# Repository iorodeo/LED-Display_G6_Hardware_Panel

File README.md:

## LED-Display\_ G6\_Hardware\_Panel 

This repository is part of <https://reiserlab.github.io/Modular-LED-Display/>.
It contains the KiCad design and production files for the G6 panel hardware.

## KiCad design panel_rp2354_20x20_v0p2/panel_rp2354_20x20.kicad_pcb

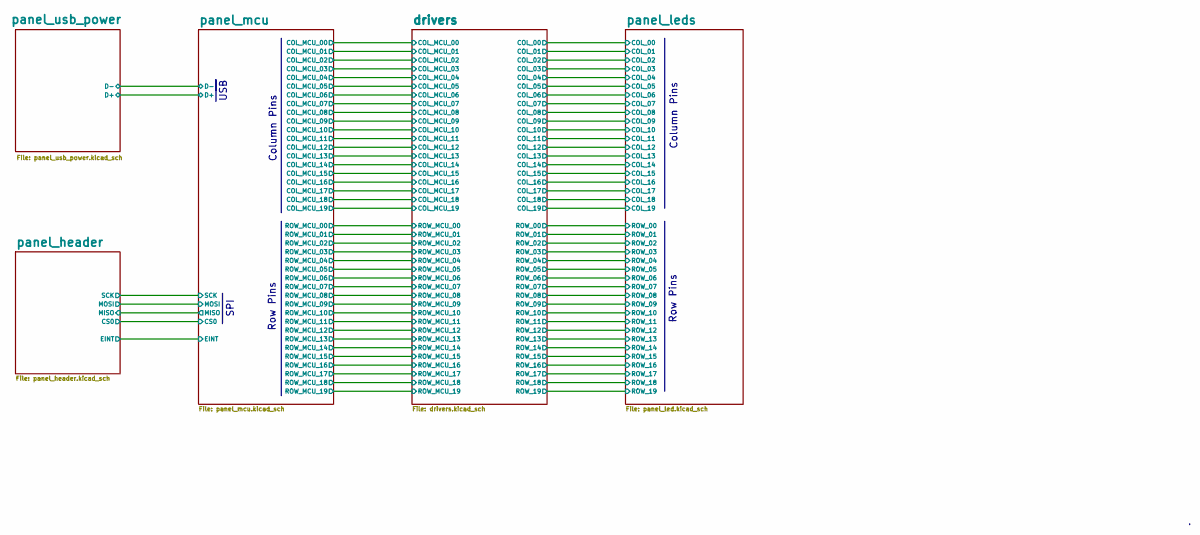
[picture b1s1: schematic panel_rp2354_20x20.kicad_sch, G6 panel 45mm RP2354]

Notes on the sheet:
Column Pins
Row Pins
SPI
USB

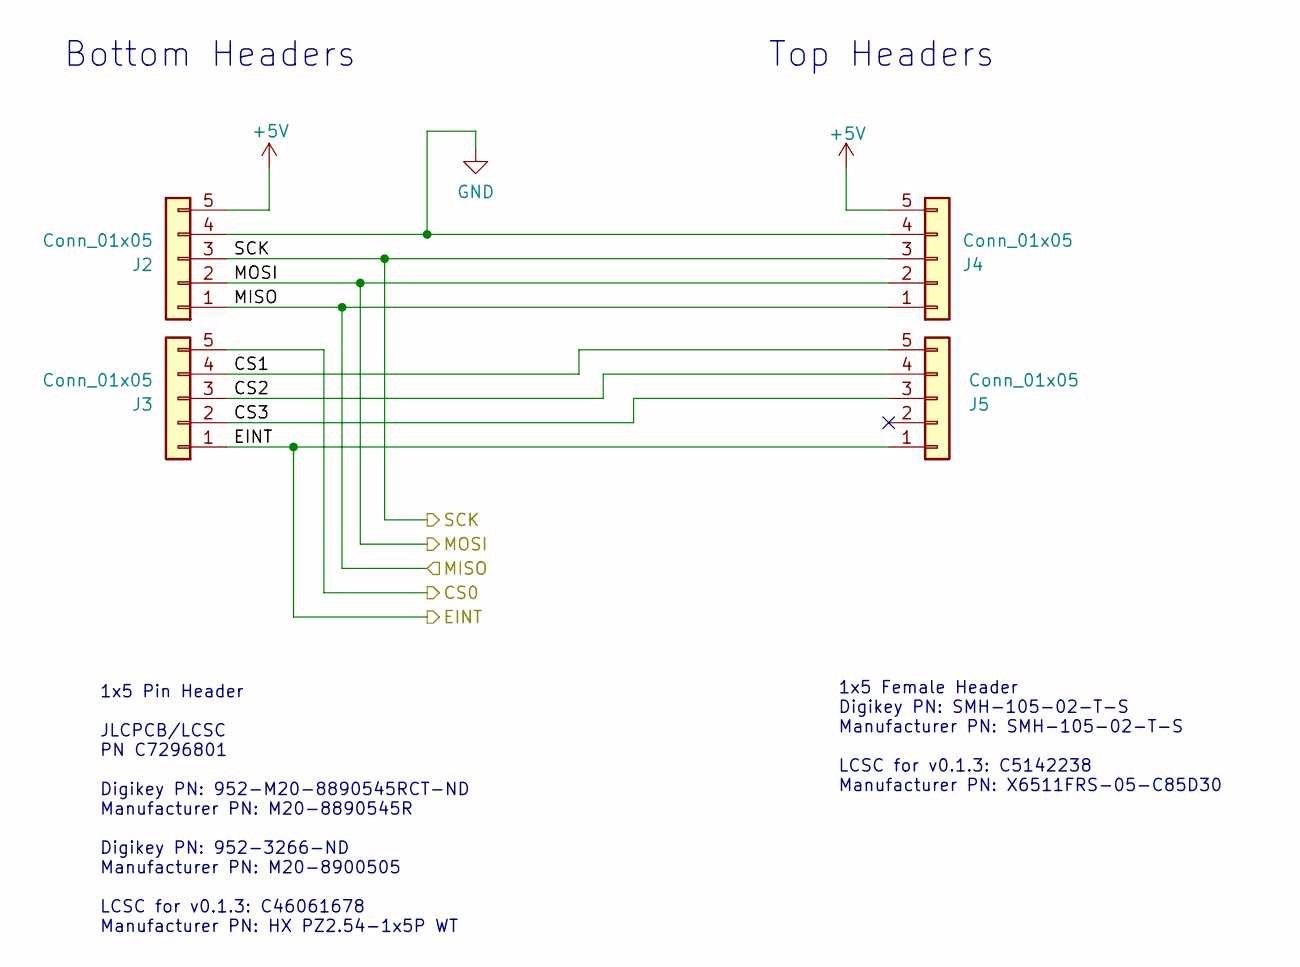
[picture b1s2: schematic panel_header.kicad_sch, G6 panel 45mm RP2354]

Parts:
J2, J3: Conn_01x05; PinHeader_1x5_M20-8890545R; LCSC Part # C46061678
J4, J5: Conn_01x05; ConnRcpt_1x5_SMH-105-02-X-S; LCSC Part # C5142238

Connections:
+5V: J2.5, J4.5; also elsewhere on the board
/panel_header/CS0: J3.5; also elsewhere on the board
/panel_header/CS1: J3.4, J5.5
/panel_header/CS2: J3.3, J5.4
/panel_header/CS3: J3.2, J5.3
/panel_header/EINT: J3.1, J5.1; also elsewhere on the board
/panel_header/MISO: J2.1, J4.1; also elsewhere on the board
/panel_header/MOSI: J2.2, J4.2; also elsewhere on the board
/panel_header/SCK: J2.3, J4.3; also elsewhere on the board
GND: J2.4, J4.4; also elsewhere on the board

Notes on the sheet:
1x5 Pin Header JLCPCB/LCSC PN C7296801 Digikey PN: 952-M20-8890545RCT-ND Manufacturer PN: M20-8890545R Digikey PN: 952-3266-ND Manufacturer PN: M20-8900505 LCSC for v0.1.3: C46061678 Manufacturer PN: HX PZ2.54-1x5P WT
Top Headers
1x5 Female Header Digikey PN: SMH-105-02-T-S Manufacturer PN: SMH-105-02-T-S LCSC for v0.1.3: C5142238 Manufacturer PN: X6511FRS-05-C85D30
Bottom Headers

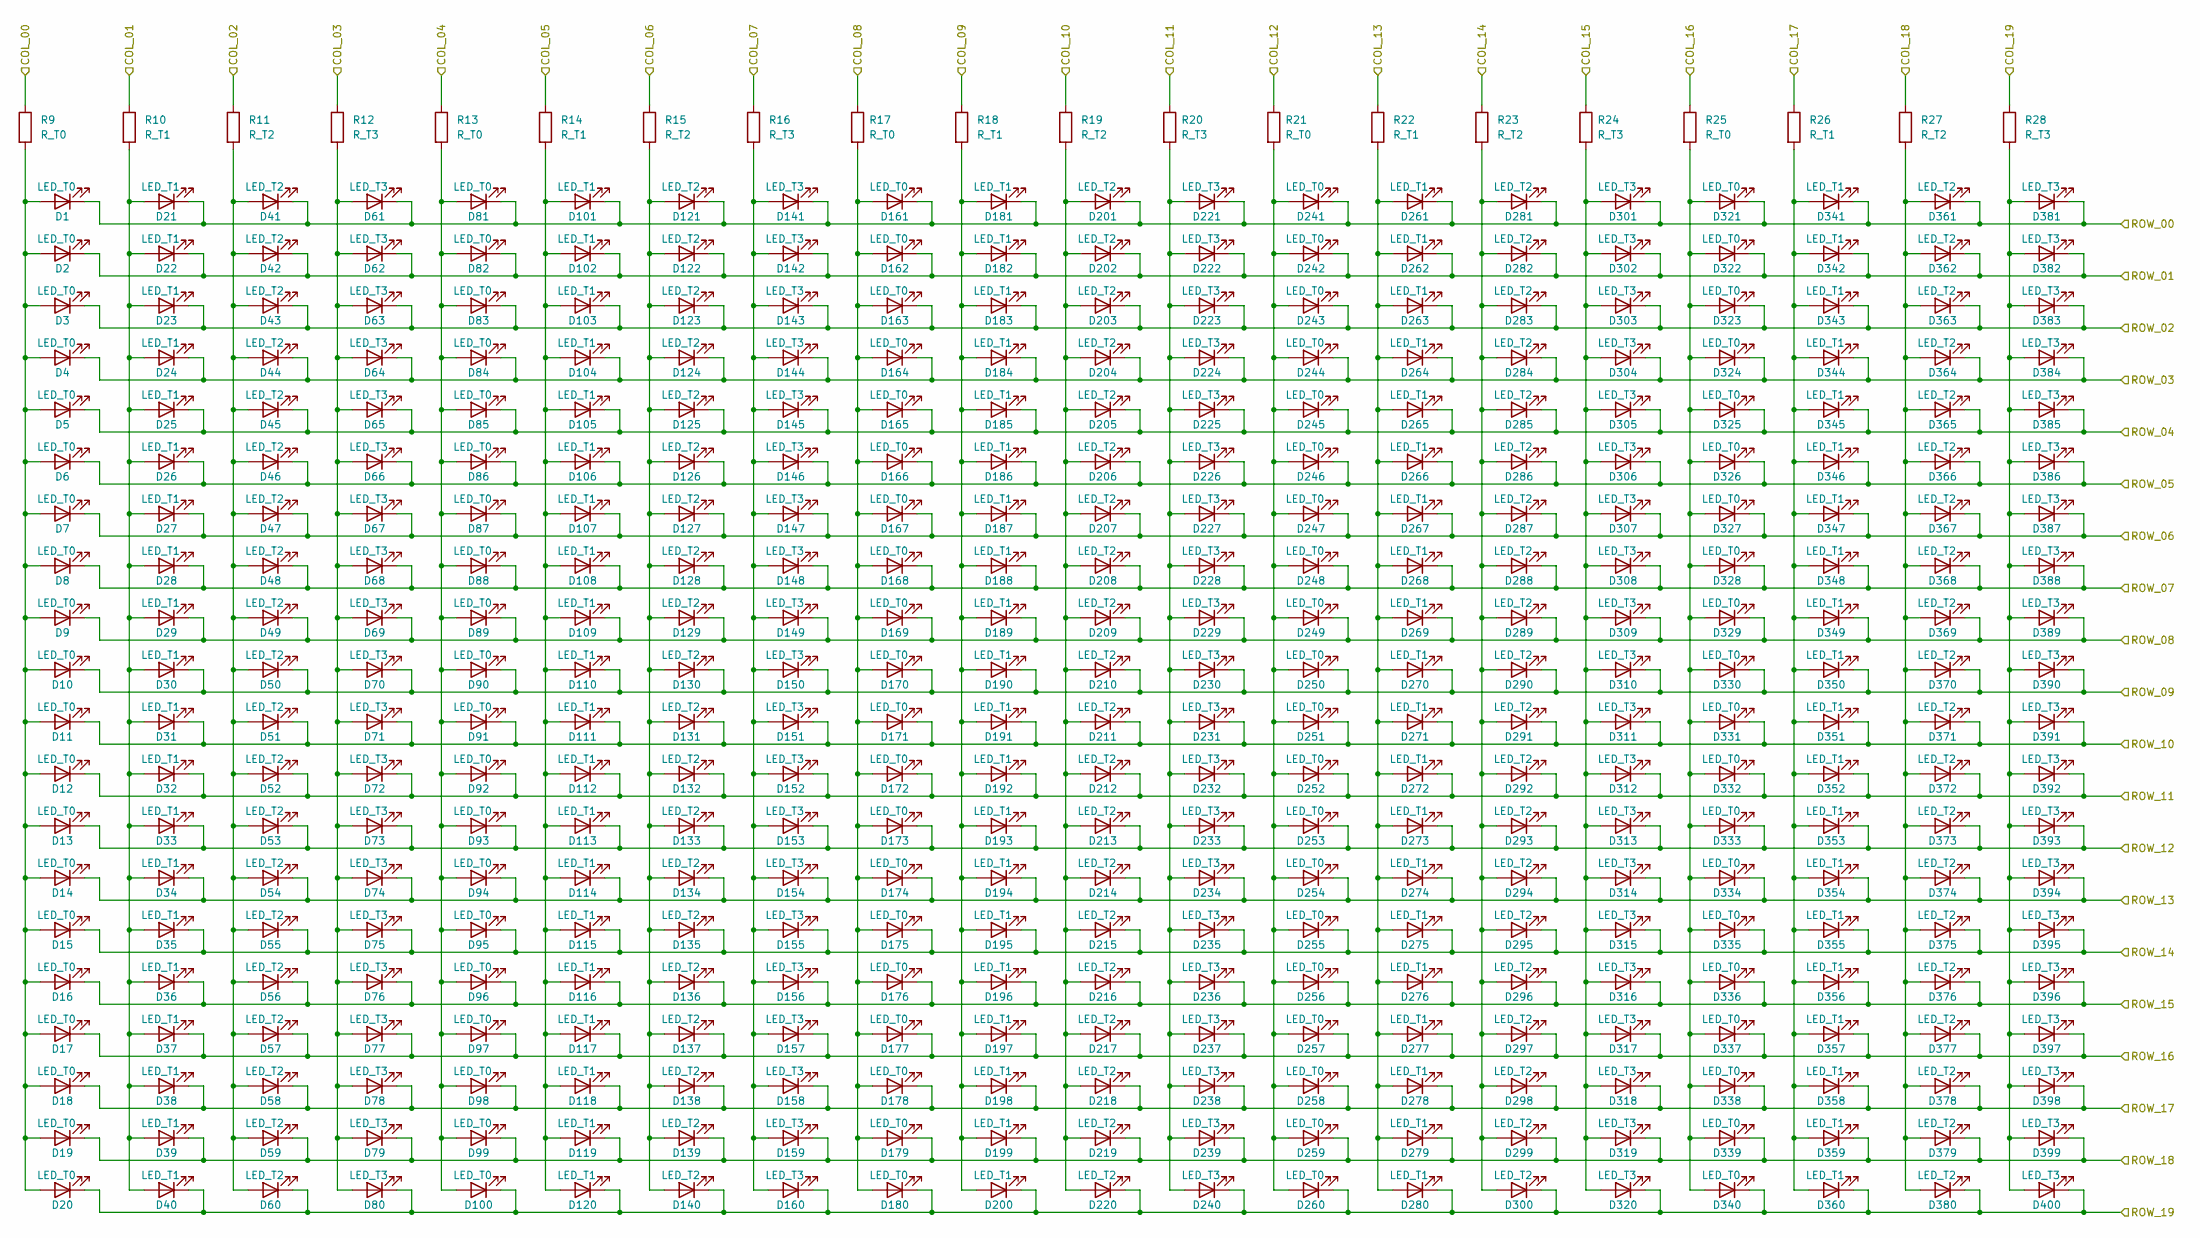
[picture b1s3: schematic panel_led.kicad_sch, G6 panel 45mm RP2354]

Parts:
D1, D2, D3, D4, D5, D6, D7, D8, D9, D10, D11, D12, D13, D14, D15, D16, D17, D18, D19, D20, D81, D82, D83, D84, D85, D86, D87, D88, D89, D90, D91, D92, D93, D94, D95, D96, D97, D98, D99, D100, D161, D162, D163, D164, D165, D166, D167, D168, D169, D170, D171, D172, D173, D174, D175, D176, D177, D178, D179, D180, D241, D242, D243, D244, D245, D246, D247, D248, D249, D250, D251, D252, D253, D254, D255, D256, D257, D258, D259, D260, D321, D322, D323, D324, D325, D326, D327, D328, D329, D330, D331, D332, D333, D334, D335, D336, D337, D338, D339, D340: LED_T0; LED_0402_1005Metric; LCSC Part # C9900113976
D21, D22, D23, D24, D25, D26, D27, D28, D29, D30, D31, D32, D33, D34, D35, D36, D37, D38, D39, D40, D101, D102, D103, D104, D105, D106, D107, D108, D109, D110, D111, D112, D113, D114, D115, D116, D117, D118, D119, D120, D181, D182, D183, D184, D185, D186, D187, D188, D189, D190, D191, D192, D193, D194, D195, D196, D197, D198, D199, D200, D261, D262, D263, D264, D265, D266, D267, D268, D269, D270, D271, D272, D273, D274, D275, D276, D277, D278, D279, D280, D341, D342, D343, D344, D345, D346, D347, D348, D349, D350, D351, D352, D353, D354, D355, D356, D357, D358, D359, D360: LED_T1; LED_0402_1005Metric; LCSC Part # C9900113976
D41, D42, D43, D44, D45, D46, D47, D48, D49, D50, D51, D52, D53, D54, D55, D56, D57, D58, D59, D60, D121, D122, D123, D124, D125, D126, D127, D128, D129, D130, D131, D132, D133, D134, D135, D136, D137, D138, D139, D140, D201, D202, D203, D204, D205, D206, D207, D208, D209, D210, D211, D212, D213, D214, D215, D216, D217, D218, D219, D220, D281, D282, D283, D284, D285, D286, D287, D288, D289, D290, D291, D292, D293, D294, D295, D296, D297, D298, D299, D300, D361, D362, D363, D364, D365, D366, D367, D368, D369, D370, D371, D372, D373, D374, D375, D376, D377, D378, D379, D380: LED_T2; LED_0402_1005Metric; LCSC Part # C9900113976
D61, D62, D63, D64, D65, D66, D67, D68, D69, D70, D71, D72, D73, D74, D75, D76, D77, D78, D79, D80, D141, D142, D143, D144, D145, D146, D147, D148, D149, D150, D151, D152, D153, D154, D155, D156, D157, D158, D159, D160, D221, D222, D223, D224, D225, D226, D227, D228, D229, D230, D231, D232, D233, D234, D235, D236, D237, D238, D239, D240, D301, D302, D303, D304, D305, D306, D307, D308, D309, D310, D311, D312, D313, D314, D315, D316, D317, D318, D319, D320, D381, D382, D383, D384, D385, D386, D387, D388, D389, D390, D391, D392, D393, D394, D395, D396, D397, D398, D399, D400: LED_T3; LED_0402_1005Metric; LCSC Part # C9900113976
R9, R13, R17, R21, R25: R_T0; R_0201_0603Metric; LCSC Part # C851657
R10, R14, R18, R22, R26: R_T1; R_0201_0603Metric; LCSC Part # C851657
R11, R15, R19, R23, R27: R_T2; R_0201_0603Metric; LCSC Part # C851657
R12, R16, R20, R24, R28: R_T3; R_0201_0603Metric; LCSC Part # C851657

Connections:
/drivers/COL_00: R9.1; also elsewhere on the board
/drivers/COL_01: R10.1; also elsewhere on the board
/drivers/COL_02: R11.1; also elsewhere on the board
/drivers/COL_03: R12.1; also elsewhere on the board
/drivers/COL_04: R13.1; also elsewhere on the board
/drivers/COL_05: R14.1; also elsewhere on the board
/drivers/COL_06: R15.1; also elsewhere on the board
/drivers/COL_07: R16.1; also elsewhere on the board
/drivers/COL_08: R17.1; also elsewhere on the board
/drivers/COL_09: R18.1; also elsewhere on the board
/drivers/COL_10: R19.1; also elsewhere on the board
/drivers/COL_11: R20.1; also elsewhere on the board
/drivers/COL_12: R21.1; also elsewhere on the board
/drivers/COL_13: R22.1; also elsewhere on the board
/drivers/COL_14: R23.1; also elsewhere on the board
/drivers/COL_15: R24.1; also elsewhere on the board
/drivers/COL_16: R25.1; also elsewhere on the board
/drivers/COL_17: R26.1; also elsewhere on the board
/drivers/COL_18: R27.1; also elsewhere on the board
/drivers/COL_19: R28.1; also elsewhere on the board
/drivers/ROW_00: D1.1 (K), D21.1 (K), D41.1 (K), D61.1 (K), D81.1 (K), D101.1 (K), D121.1 (K), D141.1 (K), D161.1 (K), D181.1 (K), D201.1 (K), D221.1 (K), D241.1 (K), D261.1 (K), D281.1 (K), D301.1 (K), D321.1 (K), D341.1 (K), D361.1 (K), D381.1 (K); also elsewhere on the board
/drivers/ROW_01: D2.1 (K), D22.1 (K), D42.1 (K), D62.1 (K), D82.1 (K), D102.1 (K), D122.1 (K), D142.1 (K), D162.1 (K), D182.1 (K), D202.1 (K), D222.1 (K), D242.1 (K), D262.1 (K), D282.1 (K), D302.1 (K), D322.1 (K), D342.1 (K), D362.1 (K), D382.1 (K); also elsewhere on the board
/drivers/ROW_02: D3.1 (K), D23.1 (K), D43.1 (K), D63.1 (K), D83.1 (K), D103.1 (K), D123.1 (K), D143.1 (K), D163.1 (K), D183.1 (K), D203.1 (K), D223.1 (K), D243.1 (K), D263.1 (K), D283.1 (K), D303.1 (K), D323.1 (K), D343.1 (K), D363.1 (K), D383.1 (K); also elsewhere on the board
/drivers/ROW_03: D4.1 (K), D24.1 (K), D44.1 (K), D64.1 (K), D84.1 (K), D104.1 (K), D124.1 (K), D144.1 (K), D164.1 (K), D184.1 (K), D204.1 (K), D224.1 (K), D244.1 (K), D264.1 (K), D284.1 (K), D304.1 (K), D324.1 (K), D344.1 (K), D364.1 (K), D384.1 (K); also elsewhere on the board
/drivers/ROW_04: D5.1 (K), D25.1 (K), D45.1 (K), D65.1 (K), D85.1 (K), D105.1 (K), D125.1 (K), D145.1 (K), D165.1 (K), D185.1 (K), D205.1 (K), D225.1 (K), D245.1 (K), D265.1 (K), D285.1 (K), D305.1 (K), D325.1 (K), D345.1 (K), D365.1 (K), D385.1 (K); also elsewhere on the board
/drivers/ROW_05: D6.1 (K), D26.1 (K), D46.1 (K), D66.1 (K), D86.1 (K), D106.1 (K), D126.1 (K), D146.1 (K), D166.1 (K), D186.1 (K), D206.1 (K), D226.1 (K), D246.1 (K), D266.1 (K), D286.1 (K), D306.1 (K), D326.1 (K), D346.1 (K), D366.1 (K), D386.1 (K); also elsewhere on the board
/drivers/ROW_06: D7.1 (K), D27.1 (K), D47.1 (K), D67.1 (K), D87.1 (K), D107.1 (K), D127.1 (K), D147.1 (K), D167.1 (K), D187.1 (K), D207.1 (K), D227.1 (K), D247.1 (K), D267.1 (K), D287.1 (K), D307.1 (K), D327.1 (K), D347.1 (K), D367.1 (K), D387.1 (K); also elsewhere on the board
/drivers/ROW_07: D8.1 (K), D28.1 (K), D48.1 (K), D68.1 (K), D88.1 (K), D108.1 (K), D128.1 (K), D148.1 (K), D168.1 (K), D188.1 (K), D208.1 (K), D228.1 (K), D248.1 (K), D268.1 (K), D288.1 (K), D308.1 (K), D328.1 (K), D348.1 (K), D368.1 (K), D388.1 (K); also elsewhere on the board
/drivers/ROW_08: D9.1 (K), D29.1 (K), D49.1 (K), D69.1 (K), D89.1 (K), D109.1 (K), D129.1 (K), D149.1 (K), D169.1 (K), D189.1 (K), D209.1 (K), D229.1 (K), D249.1 (K), D269.1 (K), D289.1 (K), D309.1 (K), D329.1 (K), D349.1 (K), D369.1 (K), D389.1 (K); also elsewhere on the board
/drivers/ROW_09: D10.1 (K), D30.1 (K), D50.1 (K), D70.1 (K), D90.1 (K), D110.1 (K), D130.1 (K), D150.1 (K), D170.1 (K), D190.1 (K), D210.1 (K), D230.1 (K), D250.1 (K), D270.1 (K), D290.1 (K), D310.1 (K), D330.1 (K), D350.1 (K), D370.1 (K), D390.1 (K); also elsewhere on the board
/drivers/ROW_10: D11.1 (K), D31.1 (K), D51.1 (K), D71.1 (K), D91.1 (K), D111.1 (K), D131.1 (K), D151.1 (K), D171.1 (K), D191.1 (K), D211.1 (K), D231.1 (K), D251.1 (K), D271.1 (K), D291.1 (K), D311.1 (K), D331.1 (K), D351.1 (K), D371.1 (K), D391.1 (K); also elsewhere on the board
/drivers/ROW_11: D12.1 (K), D32.1 (K), D52.1 (K), D72.1 (K), D92.1 (K), D112.1 (K), D132.1 (K), D152.1 (K), D172.1 (K), D192.1 (K), D212.1 (K), D232.1 (K), D252.1 (K), D272.1 (K), D292.1 (K), D312.1 (K), D332.1 (K), D352.1 (K), D372.1 (K), D392.1 (K); also elsewhere on the board
/drivers/ROW_12: D13.1 (K), D33.1 (K), D53.1 (K), D73.1 (K), D93.1 (K), D113.1 (K), D133.1 (K), D153.1 (K), D173.1 (K), D193.1 (K), D213.1 (K), D233.1 (K), D253.1 (K), D273.1 (K), D293.1 (K), D313.1 (K), D333.1 (K), D353.1 (K), D373.1 (K), D393.1 (K); also elsewhere on the board
/drivers/ROW_13: D14.1 (K), D34.1 (K), D54.1 (K), D74.1 (K), D94.1 (K), D114.1 (K), D134.1 (K), D154.1 (K), D174.1 (K), D194.1 (K), D214.1 (K), D234.1 (K), D254.1 (K), D274.1 (K), D294.1 (K), D314.1 (K), D334.1 (K), D354.1 (K), D374.1 (K), D394.1 (K); also elsewhere on the board
/drivers/ROW_14: D15.1 (K), D35.1 (K), D55.1 (K), D75.1 (K), D95.1 (K), D115.1 (K), D135.1 (K), D155.1 (K), D175.1 (K), D195.1 (K), D215.1 (K), D235.1 (K), D255.1 (K), D275.1 (K), D295.1 (K), D315.1 (K), D335.1 (K), D355.1 (K), D375.1 (K), D395.1 (K); also elsewhere on the board
/drivers/ROW_15: D16.1 (K), D36.1 (K), D56.1 (K), D76.1 (K), D96.1 (K), D116.1 (K), D136.1 (K), D156.1 (K), D176.1 (K), D196.1 (K), D216.1 (K), D236.1 (K), D256.1 (K), D276.1 (K), D296.1 (K), D316.1 (K), D336.1 (K), D356.1 (K), D376.1 (K), D396.1 (K); also elsewhere on the board
/drivers/ROW_16: D17.1 (K), D37.1 (K), D57.1 (K), D77.1 (K), D97.1 (K), D117.1 (K), D137.1 (K), D157.1 (K), D177.1 (K), D197.1 (K), D217.1 (K), D237.1 (K), D257.1 (K), D277.1 (K), D297.1 (K), D317.1 (K), D337.1 (K), D357.1 (K), D377.1 (K), D397.1 (K); also elsewhere on the board
/drivers/ROW_17: D18.1 (K), D38.1 (K), D58.1 (K), D78.1 (K), D98.1 (K), D118.1 (K), D138.1 (K), D158.1 (K), D178.1 (K), D198.1 (K), D218.1 (K), D238.1 (K), D258.1 (K), D278.1 (K), D298.1 (K), D318.1 (K), D338.1 (K), D358.1 (K), D378.1 (K), D398.1 (K); also elsewhere on the board
/drivers/ROW_18: D19.1 (K), D39.1 (K), D59.1 (K), D79.1 (K), D99.1 (K), D119.1 (K), D139.1 (K), D159.1 (K), D179.1 (K), D199.1 (K), D219.1 (K), D239.1 (K), D259.1 (K), D279.1 (K), D299.1 (K), D319.1 (K), D339.1 (K), D359.1 (K), D379.1 (K), D399.1 (K); also elsewhere on the board
/drivers/ROW_19: D20.1 (K), D40.1 (K), D60.1 (K), D80.1 (K), D100.1 (K), D120.1 (K), D140.1 (K), D160.1 (K), D180.1 (K), D200.1 (K), D220.1 (K), D240.1 (K), D260.1 (K), D280.1 (K), D300.1 (K), D320.1 (K), D340.1 (K), D360.1 (K), D380.1 (K), D400.1 (K); also elsewhere on the board
unnamed: D1.2 (A), D2.2 (A), D3.2 (A), D4.2 (A), D5.2 (A), D6.2 (A), D7.2 (A), D8.2 (A), D9.2 (A), D10.2 (A), D11.2 (A), D12.2 (A), D13.2 (A), D14.2 (A), D15.2 (A), D16.2 (A), D17.2 (A), D18.2 (A), D19.2 (A), D20.2 (A), R9.2
unnamed: D21.2 (A), D22.2 (A), D23.2 (A), D24.2 (A), D25.2 (A), D26.2 (A), D27.2 (A), D28.2 (A), D29.2 (A), D30.2 (A), D31.2 (A), D32.2 (A), D33.2 (A), D34.2 (A), D35.2 (A), D36.2 (A), D37.2 (A), D38.2 (A), D39.2 (A), D40.2 (A), R10.2
unnamed: D41.2 (A), D42.2 (A), D43.2 (A), D44.2 (A), D45.2 (A), D46.2 (A), D47.2 (A), D48.2 (A), D49.2 (A), D50.2 (A), D51.2 (A), D52.2 (A), D53.2 (A), D54.2 (A), D55.2 (A), D56.2 (A), D57.2 (A), D58.2 (A), D59.2 (A), D60.2 (A), R11.2
unnamed: D61.2 (A), D62.2 (A), D63.2 (A), D64.2 (A), D65.2 (A), D66.2 (A), D67.2 (A), D68.2 (A), D69.2 (A), D70.2 (A), D71.2 (A), D72.2 (A), D73.2 (A), D74.2 (A), D75.2 (A), D76.2 (A), D77.2 (A), D78.2 (A), D79.2 (A), D80.2 (A), R12.2
unnamed: D81.2 (A), D82.2 (A), D83.2 (A), D84.2 (A), D85.2 (A), D86.2 (A), D87.2 (A), D88.2 (A), D89.2 (A), D90.2 (A), D91.2 (A), D92.2 (A), D93.2 (A), D94.2 (A), D95.2 (A), D96.2 (A), D97.2 (A), D98.2 (A), D99.2 (A), D100.2 (A), R13.2
unnamed: D101.2 (A), D102.2 (A), D103.2 (A), D104.2 (A), D105.2 (A), D106.2 (A), D107.2 (A), D108.2 (A), D109.2 (A), D110.2 (A), D111.2 (A), D112.2 (A), D113.2 (A), D114.2 (A), D115.2 (A), D116.2 (A), D117.2 (A), D118.2 (A), D119.2 (A), D120.2 (A), R14.2
unnamed: D121.2 (A), D122.2 (A), D123.2 (A), D124.2 (A), D125.2 (A), D126.2 (A), D127.2 (A), D128.2 (A), D129.2 (A), D130.2 (A), D131.2 (A), D132.2 (A), D133.2 (A), D134.2 (A), D135.2 (A), D136.2 (A), D137.2 (A), D138.2 (A), D139.2 (A), D140.2 (A), R15.2
unnamed: D141.2 (A), D142.2 (A), D143.2 (A), D144.2 (A), D145.2 (A), D146.2 (A), D147.2 (A), D148.2 (A), D149.2 (A), D150.2 (A), D151.2 (A), D152.2 (A), D153.2 (A), D154.2 (A), D155.2 (A), D156.2 (A), D157.2 (A), D158.2 (A), D159.2 (A), D160.2 (A), R16.2
unnamed: D161.2 (A), D162.2 (A), D163.2 (A), D164.2 (A), D165.2 (A), D166.2 (A), D167.2 (A), D168.2 (A), D169.2 (A), D170.2 (A), D171.2 (A), D172.2 (A), D173.2 (A), D174.2 (A), D175.2 (A), D176.2 (A), D177.2 (A), D178.2 (A), D179.2 (A), D180.2 (A), R17.2
unnamed: D181.2 (A), D182.2 (A), D183.2 (A), D184.2 (A), D185.2 (A), D186.2 (A), D187.2 (A), D188.2 (A), D189.2 (A), D190.2 (A), D191.2 (A), D192.2 (A), D193.2 (A), D194.2 (A), D195.2 (A), D196.2 (A), D197.2 (A), D198.2 (A), D199.2 (A), D200.2 (A), R18.2
unnamed: D201.2 (A), D202.2 (A), D203.2 (A), D204.2 (A), D205.2 (A), D206.2 (A), D207.2 (A), D208.2 (A), D209.2 (A), D210.2 (A), D211.2 (A), D212.2 (A), D213.2 (A), D214.2 (A), D215.2 (A), D216.2 (A), D217.2 (A), D218.2 (A), D219.2 (A), D220.2 (A), R19.2
unnamed: D221.2 (A), D222.2 (A), D223.2 (A), D224.2 (A), D225.2 (A), D226.2 (A), D227.2 (A), D228.2 (A), D229.2 (A), D230.2 (A), D231.2 (A), D232.2 (A), D233.2 (A), D234.2 (A), D235.2 (A), D236.2 (A), D237.2 (A), D238.2 (A), D239.2 (A), D240.2 (A), R20.2
unnamed: D241.2 (A), D242.2 (A), D243.2 (A), D244.2 (A), D245.2 (A), D246.2 (A), D247.2 (A), D248.2 (A), D249.2 (A), D250.2 (A), D251.2 (A), D252.2 (A), D253.2 (A), D254.2 (A), D255.2 (A), D256.2 (A), D257.2 (A), D258.2 (A), D259.2 (A), D260.2 (A), R21.2
unnamed: D261.2 (A), D262.2 (A), D263.2 (A), D264.2 (A), D265.2 (A), D266.2 (A), D267.2 (A), D268.2 (A), D269.2 (A), D270.2 (A), D271.2 (A), D272.2 (A), D273.2 (A), D274.2 (A), D275.2 (A), D276.2 (A), D277.2 (A), D278.2 (A), D279.2 (A), D280.2 (A), R22.2
unnamed: D281.2 (A), D282.2 (A), D283.2 (A), D284.2 (A), D285.2 (A), D286.2 (A), D287.2 (A), D288.2 (A), D289.2 (A), D290.2 (A), D291.2 (A), D292.2 (A), D293.2 (A), D294.2 (A), D295.2 (A), D296.2 (A), D297.2 (A), D298.2 (A), D299.2 (A), D300.2 (A), R23.2
unnamed: D301.2 (A), D302.2 (A), D303.2 (A), D304.2 (A), D305.2 (A), D306.2 (A), D307.2 (A), D308.2 (A), D309.2 (A), D310.2 (A), D311.2 (A), D312.2 (A), D313.2 (A), D314.2 (A), D315.2 (A), D316.2 (A), D317.2 (A), D318.2 (A), D319.2 (A), D320.2 (A), R24.2
unnamed: D321.2 (A), D322.2 (A), D323.2 (A), D324.2 (A), D325.2 (A), D326.2 (A), D327.2 (A), D328.2 (A), D329.2 (A), D330.2 (A), D331.2 (A), D332.2 (A), D333.2 (A), D334.2 (A), D335.2 (A), D336.2 (A), D337.2 (A), D338.2 (A), D339.2 (A), D340.2 (A), R25.2
unnamed: D341.2 (A), D342.2 (A), D343.2 (A), D344.2 (A), D345.2 (A), D346.2 (A), D347.2 (A), D348.2 (A), D349.2 (A), D350.2 (A), D351.2 (A), D352.2 (A), D353.2 (A), D354.2 (A), D355.2 (A), D356.2 (A), D357.2 (A), D358.2 (A), D359.2 (A), D360.2 (A), R26.2
unnamed: D361.2 (A), D362.2 (A), D363.2 (A), D364.2 (A), D365.2 (A), D366.2 (A), D367.2 (A), D368.2 (A), D369.2 (A), D370.2 (A), D371.2 (A), D372.2 (A), D373.2 (A), D374.2 (A), D375.2 (A), D376.2 (A), D377.2 (A), D378.2 (A), D379.2 (A), D380.2 (A), R27.2
unnamed: D381.2 (A), D382.2 (A), D383.2 (A), D384.2 (A), D385.2 (A), D386.2 (A), D387.2 (A), D388.2 (A), D389.2 (A), D390.2 (A), D391.2 (A), D392.2 (A), D393.2 (A), D394.2 (A), D395.2 (A), D396.2 (A), D397.2 (A), D398.2 (A), D399.2 (A), D400.2 (A), R28.2

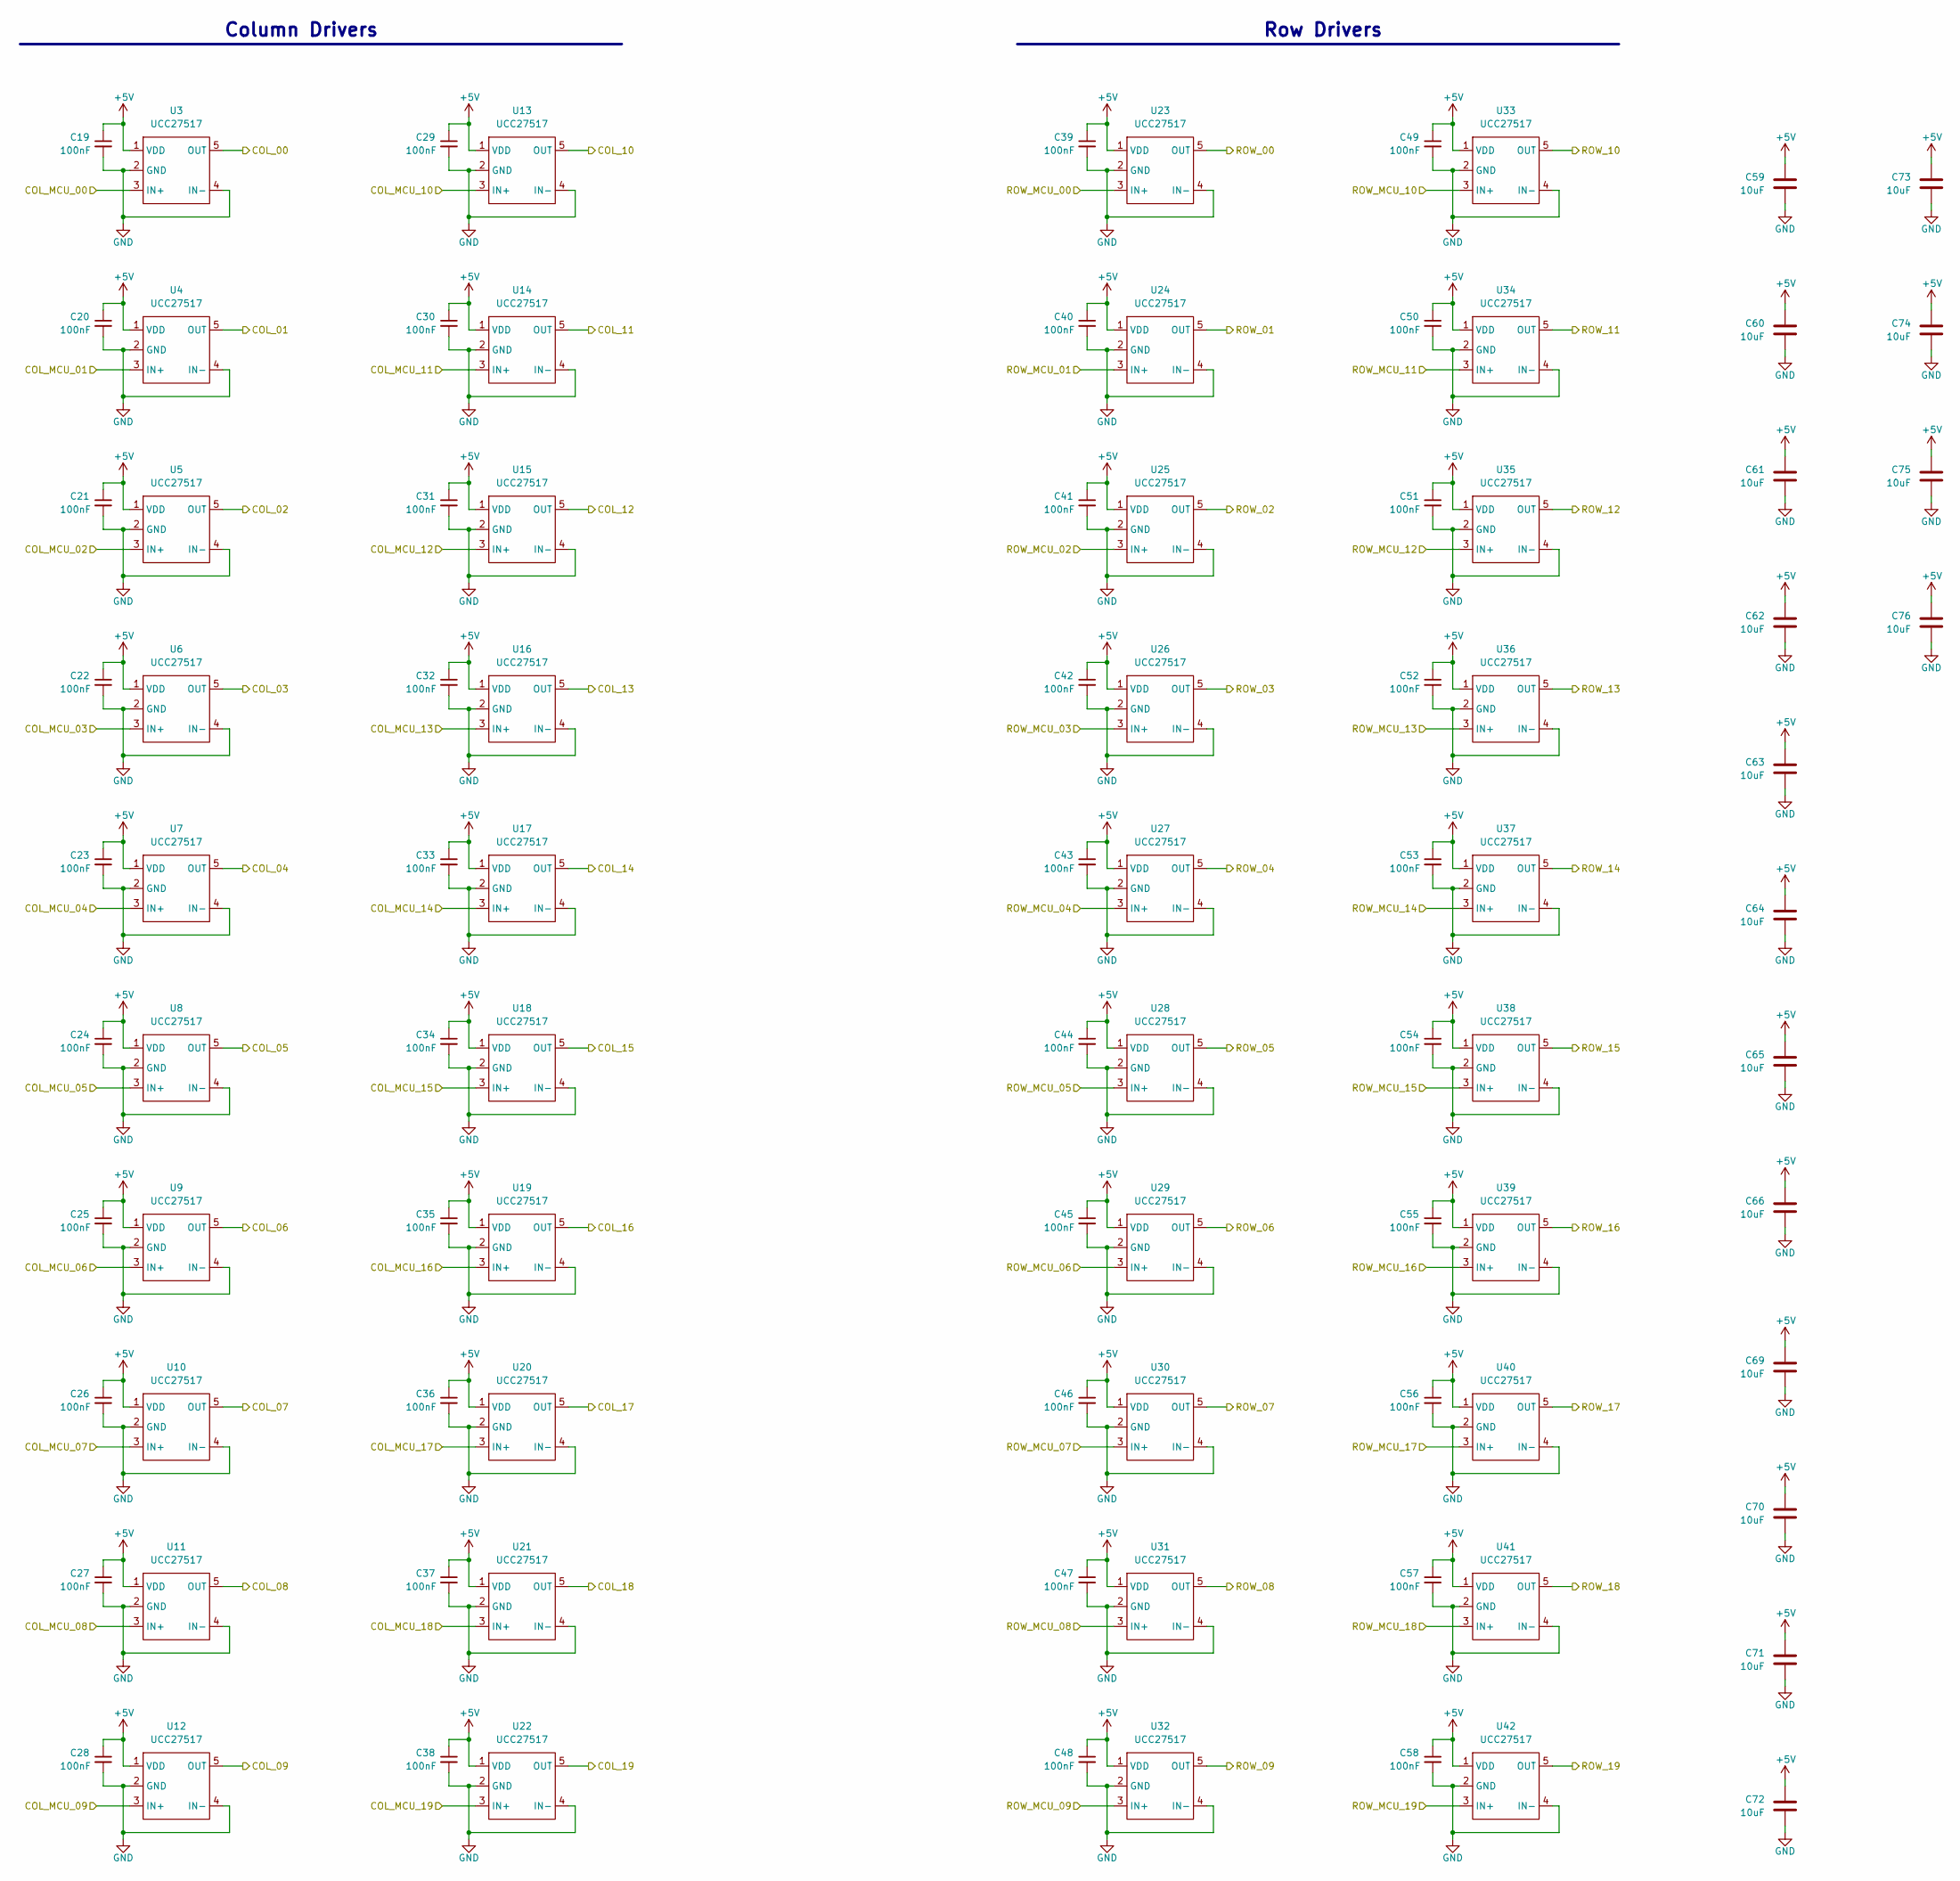
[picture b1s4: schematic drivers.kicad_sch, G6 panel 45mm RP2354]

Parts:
C19, C20, C21, C22, C23, C24, C25, C26, C27, C28, C29, C30, C31, C32, C33, C34, C35, C36, C37, C38, C39, C40, C41, C42, C43, C44, C45, C46, C47, C48, C49, C50, C51, C52, C53, C54, C55, C56, C57, C58: 100nF; C_0201_0603Metric; LCSC Part # C76939
C59, C60, C61, C62, C63, C64, C65, C66, C69, C70, C71, C72, C73, C74, C75, C76: 10uF; C_0402_1005Metric; LCSC Part # C315248
U3, U4, U5, U6, U7, U8, U9, U10, U11, U12, U13, U14, U15, U16, U17, U18, U19, U20, U21, U22, U23, U24, U25, U26, U27, U28, U29, U30, U31, U32, U33, U34, U35, U36, U37, U38, U39, U40, U41, U42: UCC27517; SOT-23-5; LCSC Part # C99395

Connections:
+5V: C19.1, C20.1, C21.1, C22.1, C23.1, C24.1, C25.1, C26.1, C27.1, C28.1, C29.1, C30.1, C31.1, C32.1, C33.1, C34.1, C35.1, C36.1, C37.1, C38.1, C39.1, C40.1, C41.1, C42.1, C43.1, C44.1, C45.1, C46.1, C47.1, C48.1, C49.1, C50.1, C51.1, C52.1, C53.1, C54.1, C55.1, C56.1, C57.1, C58.1, C59.1, C60.1, C61.1, C62.1, C63.1, C64.1, C65.1, C66.1, C69.1, C70.1, C71.1, C72.1, C73.1, C74.1, C75.1, C76.1, U3.1 (VDD), U4.1 (VDD), U5.1 (VDD), U6.1 (VDD), U7.1 (VDD), U8.1 (VDD), U9.1 (VDD), U10.1 (VDD), U11.1 (VDD), U12.1 (VDD), U13.1 (VDD), U14.1 (VDD), U15.1 (VDD), U16.1 (VDD), U17.1 (VDD), U18.1 (VDD), U19.1 (VDD), U20.1 (VDD), U21.1 (VDD), U22.1 (VDD), U23.1 (VDD), U24.1 (VDD), U25.1 (VDD), U26.1 (VDD), U27.1 (VDD), U28.1 (VDD), U29.1 (VDD), U30.1 (VDD), U31.1 (VDD), U32.1 (VDD), U33.1 (VDD), U34.1 (VDD), U35.1 (VDD), U36.1 (VDD), U37.1 (VDD), U38.1 (VDD), U39.1 (VDD), U40.1 (VDD), U41.1 (VDD), U42.1 (VDD); also elsewhere on the board
/drivers/COL_00: U3.5 (OUT); also elsewhere on the board
/drivers/COL_01: U4.5 (OUT); also elsewhere on the board
/drivers/COL_02: U5.5 (OUT); also elsewhere on the board
/drivers/COL_03: U6.5 (OUT); also elsewhere on the board
/drivers/COL_04: U7.5 (OUT); also elsewhere on the board
/drivers/COL_05: U8.5 (OUT); also elsewhere on the board
/drivers/COL_06: U9.5 (OUT); also elsewhere on the board
/drivers/COL_07: U10.5 (OUT); also elsewhere on the board
/drivers/COL_08: U11.5 (OUT); also elsewhere on the board
/drivers/COL_09: U12.5 (OUT); also elsewhere on the board
/drivers/COL_10: U13.5 (OUT); also elsewhere on the board
/drivers/COL_11: U14.5 (OUT); also elsewhere on the board
/drivers/COL_12: U15.5 (OUT); also elsewhere on the board
/drivers/COL_13: U16.5 (OUT); also elsewhere on the board
/drivers/COL_14: U17.5 (OUT); also elsewhere on the board
/drivers/COL_15: U18.5 (OUT); also elsewhere on the board
/drivers/COL_16: U19.5 (OUT); also elsewhere on the board
/drivers/COL_17: U20.5 (OUT); also elsewhere on the board
/drivers/COL_18: U21.5 (OUT); also elsewhere on the board
/drivers/COL_19: U22.5 (OUT); also elsewhere on the board
/drivers/COL_MCU_00: U3.3 (IN+); also elsewhere on the board
/drivers/COL_MCU_01: U4.3 (IN+); also elsewhere on the board
/drivers/COL_MCU_02: U5.3 (IN+); also elsewhere on the board
/drivers/COL_MCU_03: U6.3 (IN+); also elsewhere on the board
/drivers/COL_MCU_04: U7.3 (IN+); also elsewhere on the board
/drivers/COL_MCU_05: U8.3 (IN+); also elsewhere on the board
/drivers/COL_MCU_06: U9.3 (IN+); also elsewhere on the board
/drivers/COL_MCU_07: U10.3 (IN+); also elsewhere on the board
/drivers/COL_MCU_08: U11.3 (IN+); also elsewhere on the board
/drivers/COL_MCU_09: U12.3 (IN+); also elsewhere on the board
/drivers/COL_MCU_10: U13.3 (IN+); also elsewhere on the board
/drivers/COL_MCU_11: U14.3 (IN+); also elsewhere on the board
/drivers/COL_MCU_12: U15.3 (IN+); also elsewhere on the board
/drivers/COL_MCU_13: U16.3 (IN+); also elsewhere on the board
/drivers/COL_MCU_14: U17.3 (IN+); also elsewhere on the board
/drivers/COL_MCU_15: U18.3 (IN+); also elsewhere on the board
/drivers/COL_MCU_16: U19.3 (IN+); also elsewhere on the board
/drivers/COL_MCU_17: U20.3 (IN+); also elsewhere on the board
/drivers/COL_MCU_18: U21.3 (IN+); also elsewhere on the board
/drivers/COL_MCU_19: U22.3 (IN+); also elsewhere on the board
/drivers/ROW_00: U23.5 (OUT); also elsewhere on the board
/drivers/ROW_01: U24.5 (OUT); also elsewhere on the board
/drivers/ROW_02: U25.5 (OUT); also elsewhere on the board
/drivers/ROW_03: U26.5 (OUT); also elsewhere on the board
/drivers/ROW_04: U27.5 (OUT); also elsewhere on the board
/drivers/ROW_05: U28.5 (OUT); also elsewhere on the board
/drivers/ROW_06: U29.5 (OUT); also elsewhere on the board
/drivers/ROW_07: U30.5 (OUT); also elsewhere on the board
/drivers/ROW_08: U31.5 (OUT); also elsewhere on the board
/drivers/ROW_09: U32.5 (OUT); also elsewhere on the board
/drivers/ROW_10: U33.5 (OUT); also elsewhere on the board
/drivers/ROW_11: U34.5 (OUT); also elsewhere on the board
/drivers/ROW_12: U35.5 (OUT); also elsewhere on the board
/drivers/ROW_13: U36.5 (OUT); also elsewhere on the board
/drivers/ROW_14: U37.5 (OUT); also elsewhere on the board
/drivers/ROW_15: U38.5 (OUT); also elsewhere on the board
/drivers/ROW_16: U39.5 (OUT); also elsewhere on the board
/drivers/ROW_17: U40.5 (OUT); also elsewhere on the board
/drivers/ROW_18: U41.5 (OUT); also elsewhere on the board
/drivers/ROW_19: U42.5 (OUT); also elsewhere on the board
/drivers/ROW_MCU_00: U23.3 (IN+); also elsewhere on the board
/drivers/ROW_MCU_01: U24.3 (IN+); also elsewhere on the board
/drivers/ROW_MCU_02: U25.3 (IN+); also elsewhere on the board
/drivers/ROW_MCU_03: U26.3 (IN+); also elsewhere on the board
/drivers/ROW_MCU_04: U27.3 (IN+); also elsewhere on the board
/drivers/ROW_MCU_05: U28.3 (IN+); also elsewhere on the board
/drivers/ROW_MCU_06: U29.3 (IN+); also elsewhere on the board
/drivers/ROW_MCU_07: U30.3 (IN+); also elsewhere on the board
/drivers/ROW_MCU_08: U31.3 (IN+); also elsewhere on the board
/drivers/ROW_MCU_09: U32.3 (IN+); also elsewhere on the board
/drivers/ROW_MCU_10: U33.3 (IN+); also elsewhere on the board
/drivers/ROW_MCU_11: U34.3 (IN+); also elsewhere on the board
/drivers/ROW_MCU_12: U35.3 (IN+); also elsewhere on the board
/drivers/ROW_MCU_13: U36.3 (IN+); also elsewhere on the board
/drivers/ROW_MCU_14: U37.3 (IN+); also elsewhere on the board
/drivers/ROW_MCU_15: U38.3 (IN+); also elsewhere on the board
/drivers/ROW_MCU_16: U39.3 (IN+); also elsewhere on the board
/drivers/ROW_MCU_17: U40.3 (IN+); also elsewhere on the board
/drivers/ROW_MCU_18: U41.3 (IN+); also elsewhere on the board
/drivers/ROW_MCU_19: U42.3 (IN+); also elsewhere on the board
GND: C19.2, C20.2, C21.2, C22.2, C23.2, C24.2, C25.2, C26.2, C27.2, C28.2, C29.2, C30.2, C31.2, C32.2, C33.2, C34.2, C35.2, C36.2, C37.2, C38.2, C39.2, C40.2, C41.2, C42.2, C43.2, C44.2, C45.2, C46.2, C47.2, C48.2, C49.2, C50.2, C51.2, C52.2, C53.2, C54.2, C55.2, C56.2, C57.2, C58.2, C59.2, C60.2, C61.2, C62.2, C63.2, C64.2, C65.2, C66.2, C69.2, C70.2, C71.2, C72.2, C73.2, C74.2, C75.2, C76.2, U3.2 (GND), U3.4 (IN-), U4.2 (GND), U4.4 (IN-), U5.2 (GND), U5.4 (IN-), U6.2 (GND), U6.4 (IN-), U7.2 (GND), U7.4 (IN-), U8.2 (GND), U8.4 (IN-), U9.2 (GND), U9.4 (IN-), U10.2 (GND), U10.4 (IN-), U11.2 (GND), U11.4 (IN-), U12.2 (GND), U12.4 (IN-), U13.2 (GND), U13.4 (IN-), U14.2 (GND), U14.4 (IN-), U15.2 (GND), U15.4 (IN-), U16.2 (GND), U16.4 (IN-), U17.2 (GND), U17.4 (IN-), U18.2 (GND), U18.4 (IN-), U19.2 (GND), U19.4 (IN-), U20.2 (GND), U20.4 (IN-), U21.2 (GND), U21.4 (IN-), U22.2 (GND), U22.4 (IN-), U23.2 (GND), U23.4 (IN-), U24.2 (GND), U24.4 (IN-), U25.2 (GND), U25.4 (IN-), U26.2 (GND), U26.4 (IN-), U27.2 (GND), U27.4 (IN-), U28.2 (GND), U28.4 (IN-), U29.2 (GND), U29.4 (IN-), U30.2 (GND), U30.4 (IN-), U31.2 (GND), U31.4 (IN-), U32.2 (GND), U32.4 (IN-), U33.2 (GND), U33.4 (IN-), U34.2 (GND), U34.4 (IN-), U35.2 (GND), U35.4 (IN-), U36.2 (GND), U36.4 (IN-), U37.2 (GND), U37.4 (IN-), U38.2 (GND), U38.4 (IN-), U39.2 (GND), U39.4 (IN-), U40.2 (GND), U40.4 (IN-), U41.2 (GND), U41.4 (IN-), U42.2 (GND), U42.4 (IN-); also elsewhere on the board

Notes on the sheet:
Column Drivers
Row Drivers
